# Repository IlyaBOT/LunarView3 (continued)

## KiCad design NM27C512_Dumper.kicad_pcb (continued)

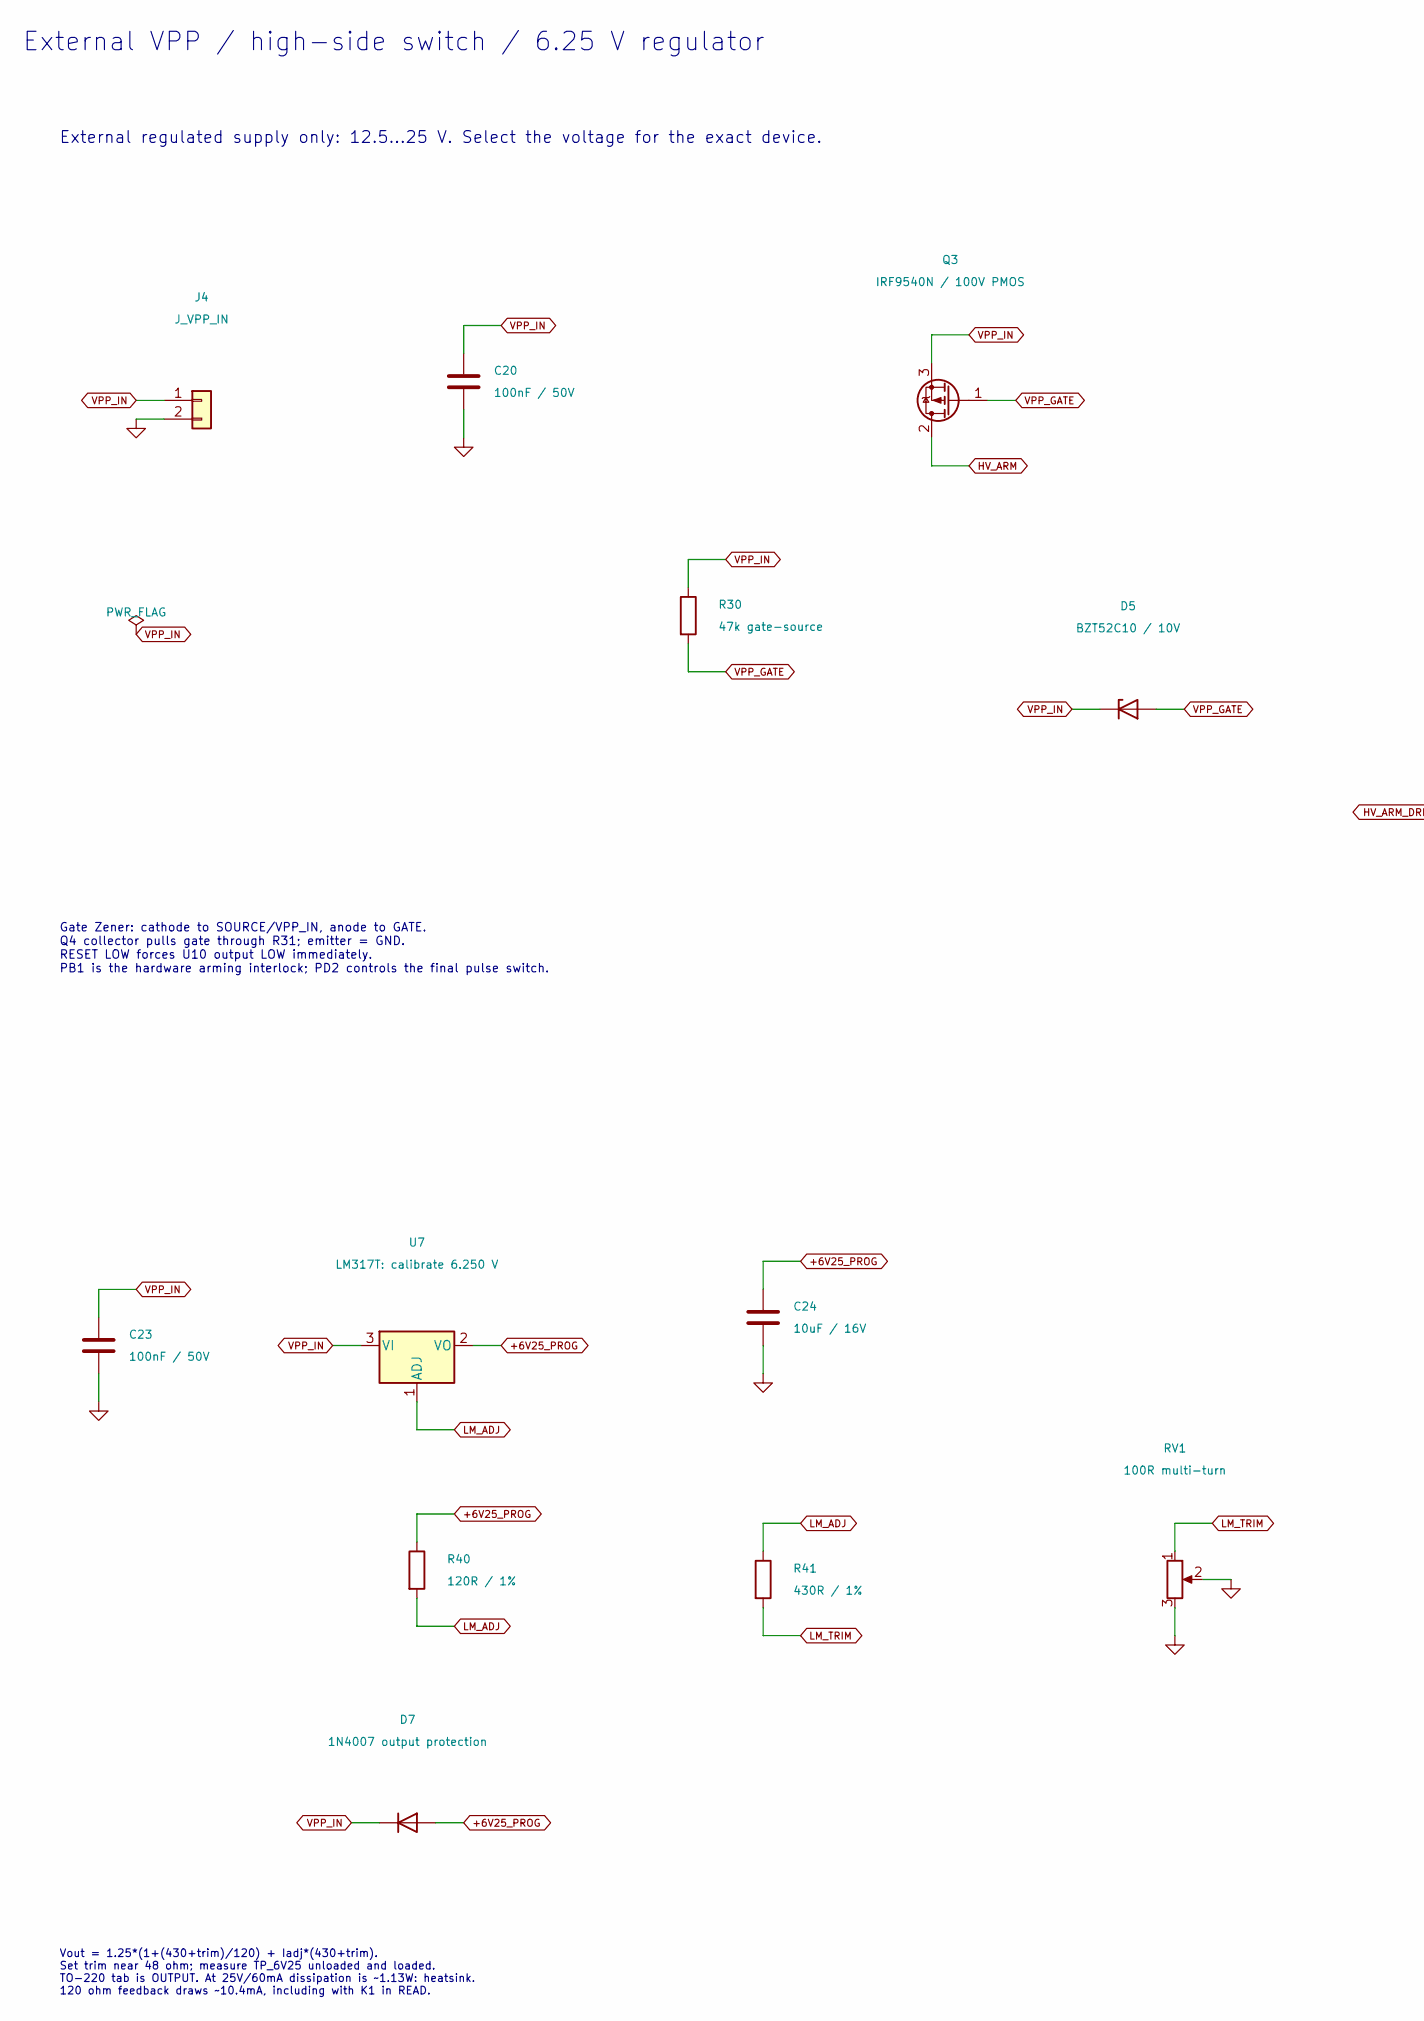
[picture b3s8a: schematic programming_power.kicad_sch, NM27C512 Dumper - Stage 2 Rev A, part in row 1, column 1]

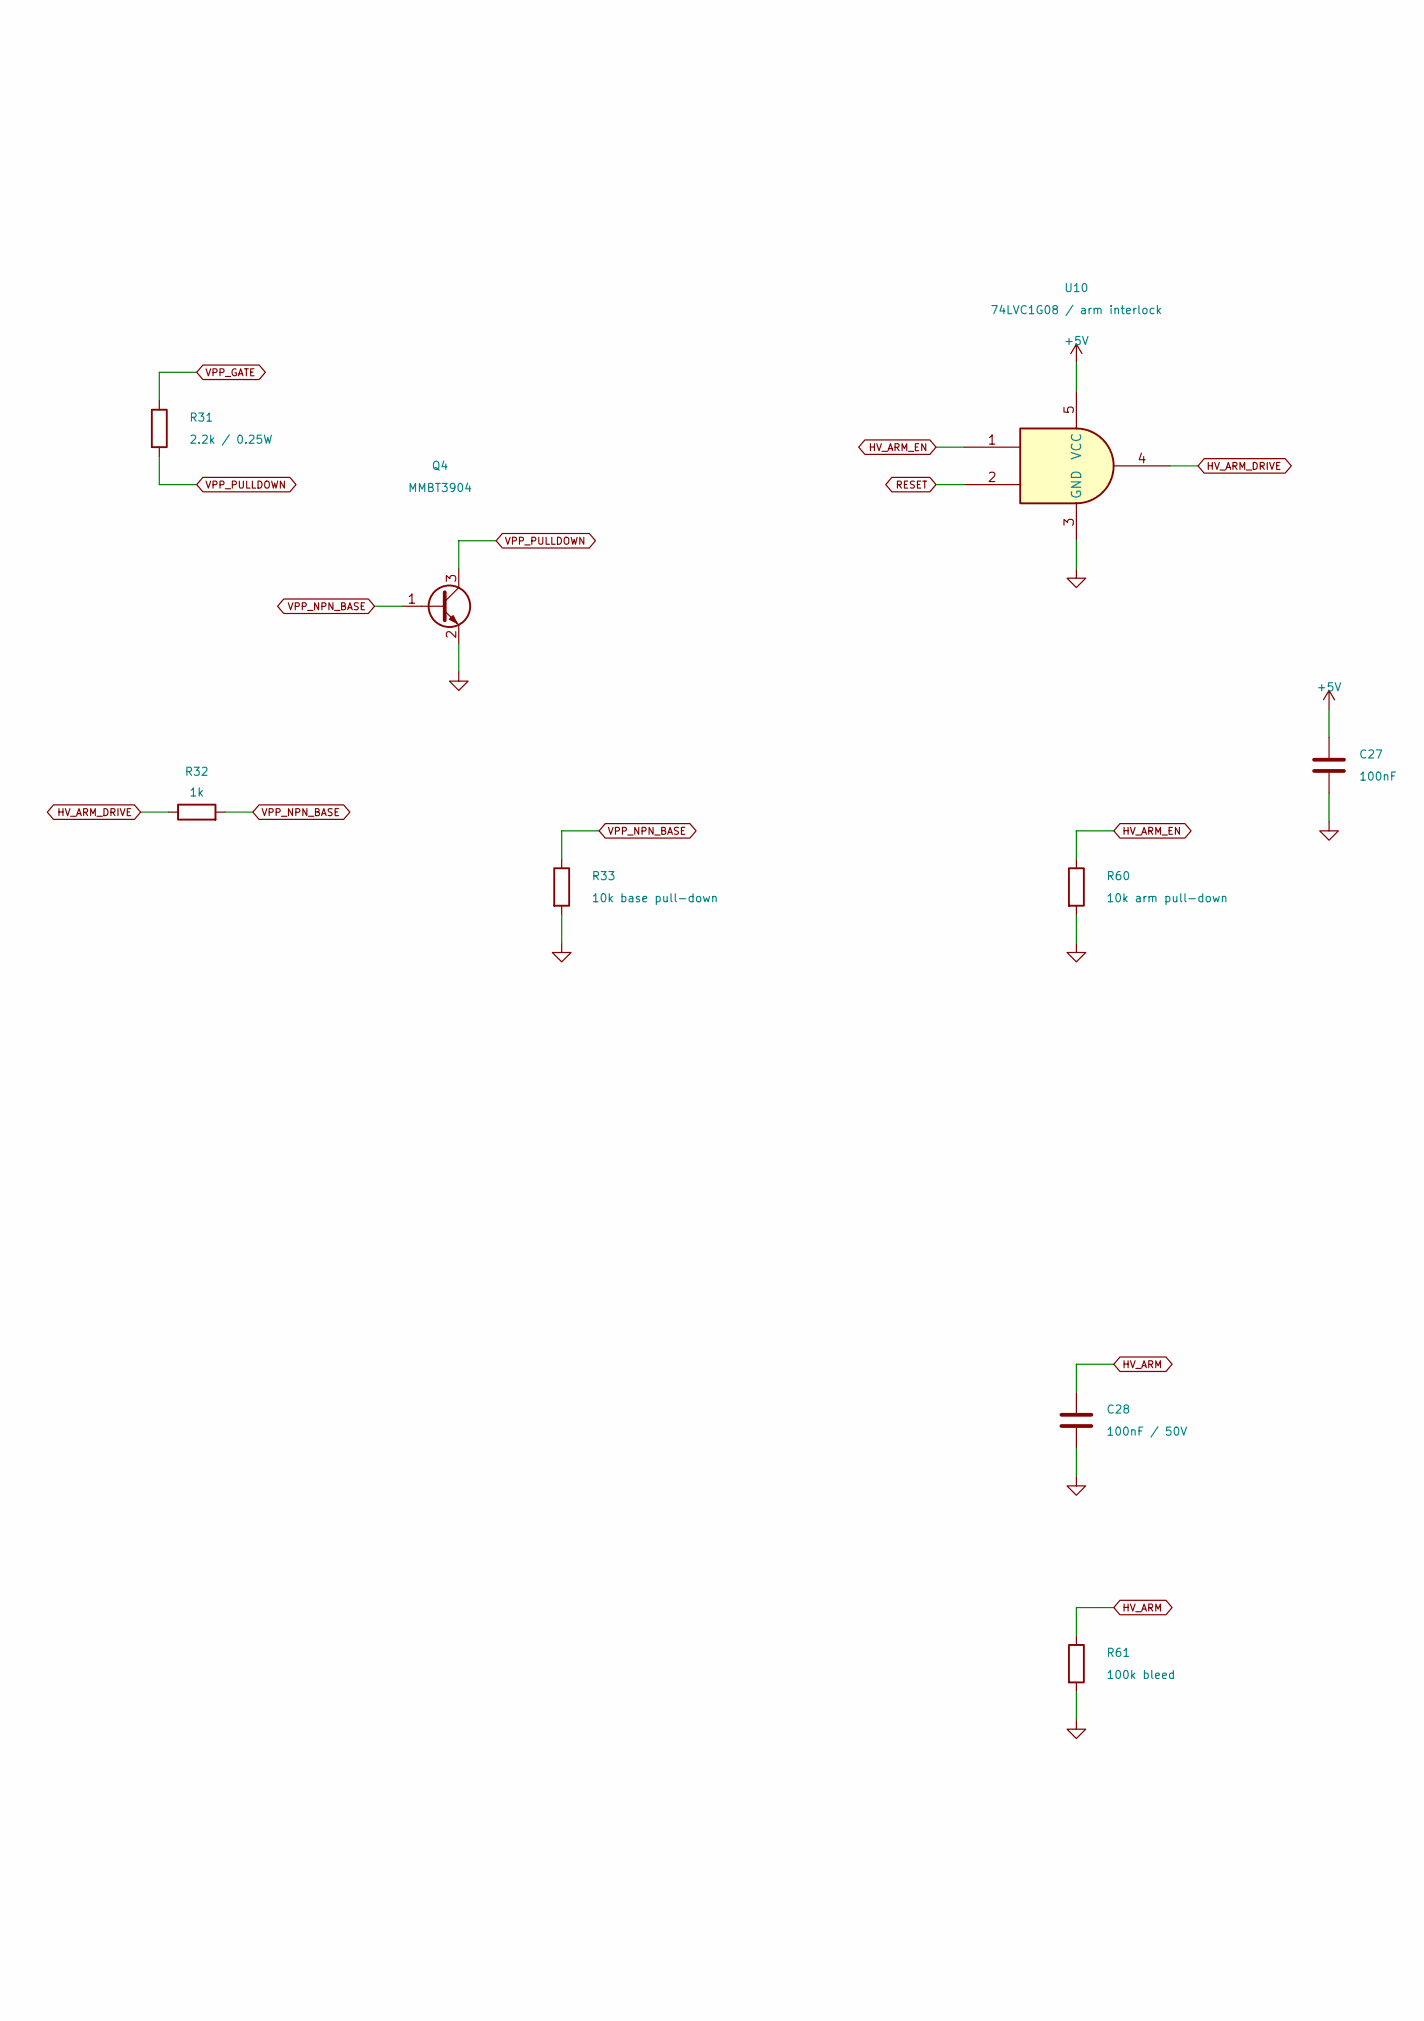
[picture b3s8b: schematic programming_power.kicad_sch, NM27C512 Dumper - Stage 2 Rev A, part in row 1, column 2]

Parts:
C20, C23, C28: 100nF / 50V; C_0603_1608Metric
C24: 10uF / 16V; C_1206_3216Metric
C27: 100nF; C_0603_1608Metric
D5: BZT52C10 / 10V; D_SOD-123
D7: 1N4007 output protection; D_DO-41_SOD81_P10.16mm_Horizontal
J4: J_VPP_IN; TerminalBlock_Phoenix_MKDS-1,5-2_1x02_P5.00mm_Horizontal
Q3: IRF9540N / 100V PMOS; TO-220-3_Vertical
Q4: MMBT3904; SOT-23
R30: 47k gate-source; R_0603_1608Metric
R31: 2.2k / 0.25W; R_1206_3216Metric
R32: 1k; R_0603_1608Metric
R33: 10k base pull-down; R_0603_1608Metric
R40: 120R / 1%; R_0603_1608Metric
R41: 430R / 1%; R_0603_1608Metric
R60: 10k arm pull-down; R_0603_1608Metric
R61: 100k bleed; R_0603_1608Metric
RV1: 100R multi-turn; Potentiometer_Bourns_3296W_Vertical
U7: LM317T: calibrate 6.250 V; TO-220-3_Vertical
U10: 74LVC1G08 / arm interlock; SOT-23-5

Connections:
+5V: C27.1, U10.5 (VCC); also elsewhere on the board
+6V25_PROG: C24.1, D7.2 (A), R40.1, U7.2 (VO); also elsewhere on the board
GND: C20.2, C23.2, C24.2, C27.2, C28.2, J4.2, Q4.2 (E), R33.2, R60.2, R61.2, RV1.2, RV1.3, U10.3 (GND); also elsewhere on the board
HV_ARM: C28.1, Q3.2 (D), R61.1; also elsewhere on the board
HV_ARM_DRIVE: R32.1, U10.4
HV_ARM_EN: R60.1, U10.1; also elsewhere on the board
LM_ADJ: R40.2, R41.1, U7.1 (ADJ)
LM_TRIM: R41.2, RV1.1
RESET: U10.2; also elsewhere on the board
VPP_GATE: D5.2 (A), Q3.1 (G), R30.2, R31.1
VPP_IN: C20.1, C23.1, D5.1 (K), D7.1 (K), J4.1, Q3.3 (S), R30.1, U7.3 (VI); also elsewhere on the board
VPP_NPN_BASE: Q4.1 (B), R32.2, R33.1
VPP_PULLDOWN: Q4.3 (C), R31.2

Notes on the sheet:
Vout = 1.25*(1+(430+trim)/120) + Iadj*(430+trim). Set trim near 48 ohm; measure TP_6V25 unloaded and loaded. TO-220 tab is OUTPUT. At 25V/60mA dissipation is ~1.13W: heatsink. 120 ohm feedback draws ~10.4mA, including with K1 in READ.
External regulated supply only: 12.5...25 V. Select the voltage for the exact device.
External VPP / high-side switch / 6.25 V regulator
Gate Zener: cathode to SOURCE/VPP_IN, anode to GATE. Q4 collector pulls gate through R31; emitter = GND. RESET LOW forces U10 output LOW immediately. PB1 is the hardware arming interlock; PD2 controls the final pulse switch.

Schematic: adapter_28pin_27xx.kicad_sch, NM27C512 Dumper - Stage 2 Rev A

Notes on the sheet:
Pin 01: 64/128/256: VPP; 512: A15
Pin 13: D2
Pin 08: A2
Pin 17: D5
Pin 05: A5
Pin 21: A10
Pin 14: GND
Pin 18: D6
2764/27128: pin27 is PGM#, NOT A14. 27256: pin27 is A14. Do not route a 595 output onto a VPP pin. Use keyed jumpers or a device-specific adapter. VPP on pin1 needs READ +5V selection, separate from the onboard NM27C512 relay. Read-only adapters may tie VPP and unused PGM# HIGH. WRITE remains disab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
Pin 03: A7
28-pin EPROM adapter reference
Pin 15: D3
Pin 27: 64/128: PGM#; 256/512: A14
Pin 16: D4
Pin 07: A3
Pin 04: A6
Pin 24: A9
Pin 02: A12
Pin 20: 64/128: CE#; 256/512: CE/PGM#
Pin 22: 64/128/256: OE#; 512: OE/VPP
REFERENCE ONLY - logical mapping for future adapter PCBs, not additional live targets
Pin 09: A1
Pin 06: A4
Pin 11: D0
Pin 12: D1
Pin 25: A8
Pin 23: A11
Pin 19: D7
Pin 10: A0
Pin 26: 64: NC; 128/256/512: A13
Pin 28: TARGET_VCC

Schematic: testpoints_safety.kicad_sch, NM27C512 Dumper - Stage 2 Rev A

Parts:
TP1: TP_5V; TestPoint_Pad_D1.5mm
TP2: TP_GND; TestPoint_Pad_D1.5mm
TP3: TP_6V25; TestPoint_Pad_D1.5mm
TP4: TP_VPP_IN; TestPoint_Pad_D1.5mm
TP5: TP_VPP_SW; TestPoint_Pad_D1.5mm
TP6: TP_RESET; TestPoint_Pad_D1.5mm
TP7: TP_ADDR_SCK; TestPoint_Pad_D1.5mm
TP8: TP_ADDR_LATCH; TestPoint_Pad_D1.5mm
TP9: TP_CE; TestPoint_Pad_D1.5mm
TP10: TP_OE; TestPoint_Pad_D1.5mm
TP11: TP_PGM; TestPoint_Pad_D1.5mm
TP12: TP_RX; TestPoint_Pad_D1.5mm
TP13: TP_TX; TestPoint_Pad_D1.5mm

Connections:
+5V: TP1.1 (1_1); also elsewhere on the board
+6V25_PROG: TP3.1 (1_1); also elsewhere on the board
ADDR_LATCH: TP8.1 (1_1); also elsewhere on the board
ADDR_SCK: TP7.1 (1_1); also elsewhere on the board
GND: TP2.1 (1_1); also elsewhere on the board
RESET: TP6.1 (1_1); also elsewhere on the board
TARGET_CE_PGM#: TP9.1 (1_1); also elsewhere on the board
TARGET_OE#: TP10.1 (1_1); also elsewhere on the board
TARGET_PGM#: TP11.1 (1_1); also elsewhere on the board
UART_RX: TP12.1 (1_1); also elsewhere on the board
UART_TX: TP13.1 (1_1); also elsewhere on the board
VPP_IN: TP4.1 (1_1); also elsewhere on the board
VPP_SW: TP5.1 (1_1); also elsewhere on the board

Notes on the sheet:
Test points and safety sequence
Safety sequence / required bench checks
1. USB supplies all 5V logic. External supply is regulated, current-limited and shares GND. 2. Power-up / RESET / ISP / DTR reset: CE and OE HIGH, relay READ, VPP disabled. 3. Preflight VPP measurement is made with relay in READ; onboard socket is isolated from VPP. 4. Verify target VCC before enab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

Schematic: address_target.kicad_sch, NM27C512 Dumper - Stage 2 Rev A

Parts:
C7, C8, C14: 100nF; C_0603_1608Metric
C9: 100nF / 16V; C_0603_1608Metric
C15: 10uF / 16V; C_0805_2012Metric
R2: 10k CE pull-up; R_0603_1608Metric
R3: 10k OE pull-up; R_0603_1608Metric
R7: 10k LATCH pull-down; R_0603_1608Metric
R8: 10k PGM pull-up; R_0603_1608Metric
U2, U3, U4: 74HC595D; SOIC-16_3.9x9.9mm_P1.27mm
U6: NM27C512Q SOCKET; DIP-28_W15.24mm_Socket_LongPads

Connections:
+5V: C7.1, C8.1, C14.1, R2.1, R3.1, R8.1, U2.10 (~SRCLR), U2.16 (VCC), U3.10 (~SRCLR), U3.16 (VCC), U4.10 (~SRCLR), U4.16 (VCC); also elsewhere on the board
A0: U2.15 (QA), U6.10 (A0); also elsewhere on the board
A1: U2.1 (QB), U6.9 (A1); also elsewhere on the board
A2: U2.2 (QC), U6.8 (A2); also elsewhere on the board
A3: U2.3 (QD), U6.7 (A3); also elsewhere on the board
A4: U2.4 (QE), U6.6 (A4); also elsewhere on the board
A5: U2.5 (QF), U6.5 (A5); also elsewhere on the board
A6: U2.6 (QG), U6.4 (A6); also elsewhere on the board
A7: U2.7 (QH), U6.3 (A7); also elsewhere on the board
A8: U3.15 (QA), U6.25 (A8); also elsewhere on the board
A9: U3.1 (QB), U6.24 (A9); also elsewhere on the board
A10: U3.2 (QC), U6.21 (A10); also elsewhere on the board
A11: U3.3 (QD), U6.23 (A11); also elsewhere on the board
A12: U3.4 (QE), U6.2 (A12); also elsewhere on the board
A13: U3.5 (QF), U6.26 (A13); also elsewhere on the board
A14: U3.6 (QG), U6.27 (A14); also elsewhere on the board
A15: U3.7 (QH), U6.1 (A15); also elsewhere on the board
A16: U4.15 (QA); also elsewhere on the board
A17: U4.1 (QB); also elsewhere on the board
A18: U4.2 (QC); also elsewhere on the board
A19: U4.3 (QD); also elsewhere on the board
ADDR_LATCH: R7.1, U2.12 (RCLK), U3.12 (RCLK), U4.12 (RCLK); also elsewhere on the board
ADDR_SCK: U2.11 (SRCLK), U3.11 (SRCLK), U4.11 (SRCLK); also elsewhere on the board
ADDR_SER: U2.14 (SER); also elsewhere on the board
CASCADE_1: U2.9 (QH'), U3.14 (SER)
CASCADE_2: U3.9 (QH'), U4.14 (SER)
GND: C7.2, C8.2, C9.2, C14.2, C15.2, R7.2, U2.8 (GND), U2.13 (~OE), U3.8 (GND), U3.13 (~OE), U4.8 (GND), U4.13 (~OE), U6.14 (GND); also elsewhere on the board
SOCKET_OE_VPP: U6.22 (~OE); also elsewhere on the board
STATUS_BLUE: U4.6 (QG); also elsewhere on the board
STATUS_GREEN: U4.5 (QF); also elsewhere on the board
STATUS_RED: U4.4 (QE); also elsewhere on the board
TARGET_CE_PGM#: R2.2, U6.20 (~CE); also elsewhere on the board
TARGET_D0: U6.11 (D0); also elsewhere on the board
TARGET_D1: U6.12 (D1); also elsewhere on the board
TARGET_D2: U6.13 (D2); also elsewhere on the board
TARGET_D3: U6.15 (D3); also elsewhere on the board
TARGET_D4: U6.16 (D4); also elsewhere on the board
TARGET_D5: U6.17 (D5); also elsewhere on the board
TARGET_D6: U6.18 (D6); also elsewhere on the board
TARGET_D7: U6.19 (D7); also elsewhere on the board
TARGET_OE#: R3.2; also elsewhere on the board
TARGET_PGM#: R8.2; also elsewhere on the board
TARGET_VCC: C9.1, C15.1, U6.28 (VCC); also elsewhere on the board

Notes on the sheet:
Address / status shift registers: SPI shifts while latch stays LOW
Send U4 byte first, U3 byte second, U2 byte last; MSB first. U2 Q0-Q7 = A0-A7; U3 Q0-Q7 = A8-A15. Stage 2: U4 Q0-Q3 = A16-A19; Q4/Q5/Q6 = active-low R/G/B. OE# = GND and SRCLR# = +5V on every 595.
Direct socket U6 is dedicated to NM27C512. One target only: socket OR adapter. Pin 20 = CE/PGM#; pin 22 = OE/VPP via K1. READ: +5V, OE logic. PROG: +6.25V, switched VPP. Do not insert/remove a target with USB or VPP connected.
Address generator and NM27C512 direct socket

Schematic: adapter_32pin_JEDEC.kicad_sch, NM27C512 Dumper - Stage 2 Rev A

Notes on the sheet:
Pin 23: A10
Pin 14: D1
Pin 22: CE / CE-PGM# (family dependent)
Pin 18: D4
Pin 08: A4
Pin 09: A3
Pin 10: A2
Pin 27: A8
Pin 07: A5
32-pin JEDEC adapter reference
Pin 19: D5
Pin 11: A1
Pin 17: D3
Pin 05: A7
Pin 25: A11
National 27C010/020/040/080 package comparison is the source for these pin roles. Use a device-specific adapter; role changes require keyed selection or HV-rated switching. Pin1 must never receive VPP when it is A19. Pin24 changes from OE to OE/VPP on 080. 27C080 cannot use a generic 32-pin VPP-pin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
Pin 02: A16
Pin 01: 010/020/040: VPP; 080: A19
Pin 06: A6
Pin 15: D2
Pin 29: A14
Pin 32: TARGET_VCC
Pin 28: A13
Pin 20: D6
Pin 31: 010/020: PGM#; 040/080: A18
Pin 03: A15
Pin 04: A12
Pin 13: D0
REFERENCE ONLY - logical mapping for future adapter PCBs, not additional live targets
Pin 12: A0
Pin 21: D7
Pin 26: A9
Pin 30: 010: NC; 020/040/080: A17
Pin 24: 010/020/040: OE#; 080: OE/VPP
Pin 16: GND

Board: 2 copper layers, 143 parts (0 on the bottom side), 113 nets, no tracks yet.

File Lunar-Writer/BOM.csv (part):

Reference,Value,Footprint,Datasheet
C1,10uF / 10V,Capacitor_SMD:C_0805_2012Metric,
C10,100nF,Capacitor_SMD:C_0603_1608Metric,
C11,22pF,Capacitor_SMD:C_0603_1608Metric,
C12,22pF,Capacitor_SMD:C_0603_1608Metric,
C13,100nF auto-reset,Capacitor_SMD:C_0603_1608Metric,
C14,100nF,Capacitor_SMD:C_0603_1608Metric,
C15,10uF / 16V,Capacitor_SMD:C_0805_2012Metric,
C2,100nF,Capacitor_SMD:C_0603_1608Metric,
C20,100nF / 50V,Capacitor_SMD:C_0603_1608Metric,
C21,100nF,Capacitor_SMD:C_0603_1608Metric,
C22,10nF,Capacitor_SMD:C_0603_1608Metric,
C23,100nF / 50V,Capacitor_SMD:C_0603_1608Metric,
C24,10uF / 16V,Capacitor_SMD:C_1206_3216Metric,
C25,10nF,Capacitor_SMD:C_0603_1608Metric,
C26,100nF,Capacitor_SMD:C_0603_1608Metric,
C27,100nF,Capacitor_SMD:C_0603_1608Metric,
C28,100nF / 50V,Capacitor_SMD:C_0603_1608Metric,
C3,100nF,Capacitor_SMD:C_0603_1608Metric,
C30,220uF / 50V low ESR,ProjectFootprints:Writer_C30_CP_Radial_D10.0mm_P5.00mm,
C31,100nF / 50V X7R,Capacitor_SMD:C_0805_2012Metric,
C32,680uF / 50V low ESR,ProjectFootprints:Writer_C32_CP_Radial_D12.5mm_P5.00mm,
C33,100nF / 50V X7R,Capacitor_SMD:C_0805_2012Metric,
C34,47uF / 16V compensation,ProjectFootprints:Writer_C34_CP_Radial_D5.0mm_P2.00mm,
C35,1uF / 50V X7R,Capacitor_SMD:C_1206_3216Metric,
C36,1uF / 50V X7R,Capacitor_SMD:C_1206_3216Metric,
C4,100nF,Capacitor_SMD:C_0603_1608Metric,
C5,100nF,Capacitor_SMD:C_0603_1608Metric,
C6,100nF,Capacitor_SMD:C_0603_1608Metric,
C7,100nF,Capacitor_SMD:C_0603_1608Metric,
C8,100nF,Capacitor_SMD:C_0603_1608Metric,
C9,100nF / 16V,Capacitor_SMD:C_0603_1608Metric,
D10,BAT54S,Package_TO_SOT_SMD:SOT-23,https://www.diodes.com/assets/Datasheets/ds11005.pdf
D11,BAT54S,Package_TO_SOT_SMD:SOT-23,https://www.diodes.com/assets/Datasheets/ds11005.pdf
D12,BAT54S,Package_TO_SOT_SMD:SOT-23,https://www.diodes.com/assets/Datasheets/ds11005.pdf
D13,BAT54S,Package_TO_SOT_SMD:SOT-23,https://www.diodes.com/assets/Datasheets/ds11005.pdf
D14,BAT54S,Package_TO_SOT_SMD:SOT-23,https://www.diodes.com/assets/Datasheets/ds11005.pdf
D15,BAT54S,Package_TO_SOT_SMD:SOT-23,https://www.diodes.com/assets/Datasheets/ds11005.pdf
D16,BAT54S,Package_TO_SOT_SMD:SOT-23,https://www.diodes.com/assets/Datasheets/ds11005.pdf
D17,BAT54S,Package_TO_SOT_SMD:SOT-23,https://www.diodes.com/assets/Datasheets/ds11005.pdf
D2,RGB CA / 5050 OR THT5,ProjectFootprints:Writer_D2_RGB_CA_5050_or_THT5,https://www.kingbright.com/attachments/file/psearch/000/00/2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
D20,BAT54S,Package_TO_SOT_SMD:SOT-23,https://www.diodes.com/assets/Datasheets/ds11005.pdf
D21,BAT54S,Package_TO_SOT_SMD:SOT-23,https://www.diodes.com/assets/Datasheets/ds11005.pdf
D22,BAT54S,Package_TO_SOT_SMD:SOT-23,https://www.diodes.com/assets/Datasheets/ds11005.pdf
D23,BAT54S,Package_TO_SOT_SMD:SOT-23,https://www.diodes.com/assets/Datasheets/ds11005.pdf
D24,BAT54S,Package_TO_SOT_SMD:SOT-23,https://www.diodes.com/assets/Datasheets/ds11005.pdf
D25,BAT54S,Package_TO_SOT_SMD:SOT-23,https://www.diodes.com/assets/Datasheets/ds11005.pdf
D26,BAT54S,Package_TO_SOT_SMD:SOT-23,https://www.diodes.com/assets/Datasheets/ds11005.pdf
D27,BAT54S,Package_TO_SOT_SMD:SOT-23,https://www.diodes.com/assets/Datasheets/ds11005.pdf
D3,RX BLUE,LED_SMD:LED_0603_1608Metric,
D30,ADC6 BAT54S clamp,Package_TO_SOT_SMD:SOT-23,https://www.diodes.com/assets/Datasheets/ds11005.pdf
D31,ADC7 BAT54S clamp,Package_TO_SOT_SMD:SOT-23,https://www.diodes.com/assets/Datasheets/ds11005.pdf
D4,TX ORANGE,LED_SMD:LED_0603_1608Metric,
D40,SS36 / 3A / 60V reverse-polarity,Diode_SMD:D_SMA,
D41,SMBJ24A / TVS,Diode_SMD:D_SMB,
D42,SS36 / 3A / 60V boost rectifier,Diode_SMD:D_SMA,
D43,M7 / 1N4007-SMD / 1A 1000V,Diode_SMD:D_SMA,
D44,M7 / 1N4007-SMD / 1A 1000V,Diode_SMD:D_SMA,
D5,BZT52C10 / 10V,Diode_SMD:D_SOD-123,
D6,VPP ACTIVE RED,LED_SMD:LED_0603_1608Metric,
D7,1N4007 output protection,ProjectFootprints:Writer_D7_D_DO-41_SOD81_P10.16mm_Horizontal,
D8,1N4148WS flyback,Diode_SMD:D_SOD-323,
D9,BAT54WS RESET clamp,Diode_SMD:D_SOD-323,
F1,500mA hold,Fuse:Fuse_1812_4532Metric,
F2,MF-R090 / 0.9A hold / 60V,ProjectFootprints:PTC_MF_R090,
J1,USB Micro-B,ProjectFootprints:Writer_J1_USB_Micro-B_Molex-105017-0001,
J2,AVR ISP,ProjectFootprints:Writer_J2_PinHeader_2x03_P2.54mm_Vertical,
J3,UART (MCU RX/TX),ProjectFootprints:Writer_J3_PinHeader_1x03_P2.54mm_Vertical,
J4,12-24V DC IN (+ / GND),"ProjectFootprints:Writer_J4_TerminalBlock_Phoenix_MKDS-1,5-2_1x02_P5.00mm_Horizontal",
J5,J_TARGET / 40-pin,ProjectFootprints:Writer_J5_PinHeader_2x20_P2.54mm_Vertical,
JP1,VPP SELECT: 12.75 / common / HIGH,ProjectFootprints:Writer_JP1_PinHeader_1x03_P2.54mm_Vertical,
K1,G5V-2-DC5 (100mA coil),ProjectFootprints:Writer_K1_Relay_DPDT_Omron_G5V-2,http://omronfs.omron.com/en_US/ecb/products/pdf/en-g5v_2.pdf
L1,100uH / SRR1210A-101M / Isat 2.2A,ProjectFootprints:Writer_L1_L_Bourns_SRR1210A,
Q1,MMBT3906,Package_TO_SOT_SMD:SOT-23,https://www.onsemi.com/pdf/datasheet/pzt3906-d.pdf
Q2,MMBT3906,Package_TO_SOT_SMD:SOT-23,https://www.onsemi.com/pdf/datasheet/pzt3906-d.pdf
Q3,IRF9540N / 100V PMOS,ProjectFootprints:Writer_Q3_TO-220-3_Vertical,http://www.irf.com/product-info/datasheets/data/irf9540n.pdf
Q4,MMBT5551 / 160V NPN,Package_TO_SOT_SMD:SOT-23,https://www.onsemi.com/pdf/datasheet/pzt3904-d.pdf
Q5,MMBT3904,Package_TO_SOT_SMD:SOT-23,https://www.onsemi.com/pdf/datasheet/pzt3904-d.pdf
Q6,MMBT5551 / 160V NPN,Package_TO_SOT_SMD:SOT-23,
Q7,MMBT5401 / 150V PNP,Package_TO_SOT_SMD:SOT-23,
R1,10k,Resistor_SMD:R_0603_1608Metric,
R10,1k,Resistor_SMD:R_0603_1608Metric,
R11,1k,Resistor_SMD:R_0603_1608Metric,
R12,1k,Resistor_SMD:R_0603_1608Metric,
R13,1k,Resistor_SMD:R_0603_1608Metric,
R14,1k,Resistor_SMD:R_0603_1608Metric,
R15,1k,Resistor_SMD:R_0603_1608Metric,
R16,1k,Resistor_SMD:R_0603_1608Metric,
R17,1k,Resistor_SMD:R_0603_1608Metric,
R2,10k CE pull-up,Resistor_SMD:R_0603_1608Metric,
R20,1k,Resistor_SMD:R_0603_1608Metric,
R21,1k,Resistor_SMD:R_0603_1608Metric,
R22,1k,Resistor_SMD:R_0603_1608Metric,
R23,10k,Resistor_SMD:R_0603_1608Metric,
R24,10k,Resistor_SMD:R_0603_1608Metric,
R25,1k,Resistor_SMD:R_0603_1608Metric,
R26,1k,Resistor_SMD:R_0603_1608Metric,
R3,10k OE pull-up,Resistor_SMD:R_0603_1608Metric,
R30,47k gate-source,Resistor_SMD:R_0603_1608Metric,
R31,2.2k / 0.5W,Resistor_SMD:R_2010_5025Metric,
R32,1k,Resistor_SMD:R_0603_1608Metric,
R33,10k base pull-down,Resistor_SMD:R_0603_1608Metric,
R34,10k VPP_EN pull-down,Resistor_SMD:R_0603_1608Metric,
R35,120k / 1%,Resistor_SMD:R_0603_1608Metric,
R36,22k / 1%,Resistor_SMD:R_0603_1608Metric,
R37,10k bleed / 0.25W,Resistor_SMD:R_1206_3216Metric,
R38,5.1k,Resistor_SMD:R_0603_1608Metric,
R39,5.1k,Resistor_SMD:R_0603_1608Metric,
R4,1k,Resistor_SMD:R_0603_1608Metric,
R40,120R / 1%,Resistor_SMD:R_0603_1608Metric,
R41,430R / 1%,Resistor_SMD:R_0603_1608Metric,
R42,470R relay drive,Resistor_SMD:R_0603_1608Metric,
R43,10k,Resistor_SMD:R_0603_1608Metric,
R44,10k,Resistor_SMD:R_0603_1608Metric,
R45,10k / 1%,Resistor_SMD:R_0603_1608Metric,
R46,10k / 1%,Resistor_SMD:R_0603_1608Metric,
R5,1k,Resistor_SMD:R_0603_1608Metric,
R50,1k,Resistor_SMD:R_0603_1608Metric,
R51,1k,Resistor_SMD:R_0603_1608Metric,
R52,1k,Resistor_SMD:R_0603_1608Metric,
R53,1k,Resistor_SMD:R_0603_1608Metric,
R54,1k,Resistor_SMD:R_0603_1608Metric,
R55,1k,Resistor_SMD:R_0603_1608Metric,
R56,1k,Resistor_SMD:R_0603_1608Metric,
R57,1k,Resistor_SMD:R_0603_1608Metric,
R60,10k arm pull-down,Resistor_SMD:R_0603_1608Metric,
R61,100k bleed,Resistor_SMD:R_0603_1608Metric,
R62,10k base-emitter,Resistor_SMD:R_0603_1608Metric,
R63,2.2k / 0.5W,Resistor_SMD:R_2010_5025Metric,
R64,1k,Resistor_SMD:R_0603_1608Metric,
R65,10k,Resistor_SMD:R_0603_1608Metric,
R7,10k LATCH pull-down,Resistor_SMD:R_0603_1608Metric,
R70,47k / 1%,Resistor_SMD:R_0603_1608Metric,
R71,2k / 1%,Resistor_SMD:R_0603_1608Metric,
R72,470R compensation,Resistor_SMD:R_0603_1608Metric,
R73,120R / 1%,Resistor_SMD:R_0603_1608Metric,
R74,1k / 1%,Resistor_SMD:R_0603_1608Metric,
R75,120R / 1%,Resistor_SMD:R_0603_1608Metric,
R76,1.8k / 1%,Resistor_SMD:R_0603_1608Metric,
R77,100k bleed,Resistor_SMD:R_0603_1608Metric,
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
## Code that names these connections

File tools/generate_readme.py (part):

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    mcu=next(p for p in bom if p['ref']=='U1')['nets']
    eprom=next(p for p in bom if p['ref']=='U6')['nets']
    header=json.loads((ROOT/'validation/target_header.json').read_text())
    gpio=['PD3','PD4','GND','VCC','GND','VCC','PB6 / XTAL1','PB7 / XTAL2','PD5','PD6','PD7','PB0','PB1','PB2','PB3 / MOSI','PB4 / MISO',
          'PB5 / SCK','AVCC','ADC6','AREF','GND','ADC7','PC0','PC1','PC2','PC3','PC4','PC5','PC6 / RESET','PD0 / RXD','PD1 / TXD','PD2']
    group=defaultdict(list)
    for part in bom:group[part['value'],part['footprint']].append(part['ref'])
    bom_table=table(['Refs','Qty','Value / exact part','KiCad footprint'],[(', '.join(refs),len(refs),value,fp) for (value,fp),refs in group.items()])
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
## ATmega328P-AU TQFP32 map

PB1, originally reserved for an interlock, now explicitly controls HV_ARM_EN. PB4/MISO is used only by ISP. ADC6/ADC7 are analog-only package pins.

'''+table(['Package pin','Function','Net'],[(i,gpio[i-1],mcu[str(i)]) for i in range(1,33)])+'''
## Address and status chain
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| Q1 / pin1 | A1 | A9 | A17 |
| Q2 / pin2 | A2 | A10 | A18 |
| Q3 / pin3 | A3 | A11 | A19 |
| Q4 / pin4 | A4 | A12 | STATUS_RED |
| Q5 / pin5 | A5 | A13 | STATUS_GREEN |
| Q6 / pin6 | A6 | A14 | STATUS_BLUE |
| Q7 / pin7 | A7 | A15 | NC / reserved |

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
'''+table(['Pin','Net','Pin','Net'],[(i,eprom[str(i)],29-i,eprom[str(29-i)]) for i in range(1,15)])+'''
In READ, TARGET_VCC=+5V and SOCKET_OE_VPP follows TARGET_OE#. In PROGRAM, TARGET_VCC=+6.25V and SOCKET_OE_VPP=VPP_SW. Pin20 CE/PGM# is the programming-pulse input. R2/R3/R8 pull CE/OE/PGM HIGH from the logic rail during RESET. K1 physically disconnects the MCU OE path from VPP.

## Headers and UART

J2 is the standard AVR ISP 2x3: pin1 MISO, 2 +5V, 3 SCK, 4 MOSI, 5 RESET, 6 GND. J3 is a 1x3 header: **1 GND, 2 RX (MCU PD0), 3 TX (MCU PD1)**. An external UART TX goes to J3 RX and external RX to J3 TX. Use 5 V TTL and avoid simultaneous active TX sources.

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
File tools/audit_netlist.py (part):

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            expect('U9',{i+2:'HCT_A'+str(i),18-i:'HCT_B'+str(i)})
            expect('R'+str(50+i),{1:'TARGET_D'+str(i),2:'HCT_B'+str(i)})
            expect('D'+str(20+i),{1:'GND',2:'+5V',3:'HCT_B'+str(i)})
        for ref,mapping in {'R35':{1:'VPP_SW',2:'VPP_SENSE'},'R36':{1:'VPP_SENSE',2:'GND'},
                            'R45':{1:'TARGET_VCC',2:'TARGET_VCC_SENSE'},'R46':{1:'TARGET_VCC_SENSE',2:'GND'}}.items():expect(ref,mapping)
        header={i+1:'A'+str(i) for i in range(20)}
        header.update({21+i:'TARGET_D'+str(i) for i in range(8)})
        header.update(dict(zip(range(29,41),['TARGET_CE_PGM#','TARGET_OE#','TARGET_PGM#','VPP_SW','TARGET_VCC','+5V','+6V25_PROG','GND','PROG_MODE','GND','RESET','GND'])))
        expect('J5',header)
        for name in ['VPP_IN','VPP_GATE','VPP_PULLDOWN','HV_ARM','VPP_SW','PULSE_PNP_BASE','PULSE_PULLDOWN','+6V25_PROG','TARGET_VCC','SOCKET_OE_VPP']:
            check(not any(ref=='U1' for ref,pin in nets.get(name,set())),f'No direct high voltage net {name} at U1')
        check(nets['ISP_MISO']=={('U1','16'),('J2','1')},'PB4/MISO used only for ISP')
    else:
        check(not any(name in nets for name in ['VPP_IN','VPP_SW','+6V25_PROG','HV_ARM']),'Baseline contains no programming rails')
    components={c.attrib['ref']:c for c in tree.findall('./components/comp')}
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
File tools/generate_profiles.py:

"""Single source of truth: generate JSON profiles and a compact AVR flash table."""
from pathlib import Path
import hashlib
import json

ROOT=Path(__file__).resolve().parents[1]
NATIONAL='https://deramp.com/downloads/mfe_archive/050-Component%20Specifications/National%20Semiconductor/Memory%20Components/'
INTEL='https://deramp.com/downloads/mfe_archive/050-Component%20Specifications/Intel/Memory%20Components/'

def profile(name, bits, package, adapter, source=None, aliases=(), verified=False):
    return dict(name=name,aliases=list(aliases),package=package,adapter=adapter,size_bytes=1<<bits,data_bits=8,address_bits=bits,
        read_supported=verified,read_vcc=5.0,read_vpp=5.0,program_supported=False,program_vcc=None,program_vpp=None,vpp_tolerance=None,
        address_pin_map={},data_pin_map={},ce_role=None,oe_role=None,pgm_role=None,vpp_pin_role=None,
        program_pulse_us=None,max_program_pulses=None,verify_algorithm=None,power_sequence=['USB logic first','controls inactive','VPP off','READ relay'],
        sources=[source] if source else [],pinout_verified=verified,read_profile_verified=verified,program_algorithm_verified=False,
        hardware_commissioned=False,read_access_delay_us=10,notes=[])

def map24(p, is2732=False):
    p['address_pin_map']={f'A{i}':8-i for i in range(8)}
    p['address_pin_map'].update(A8=23,A9=22,A10=19)
    if is2732:p['address_pin_map']['A11']=21
    p['data_pin_map']={f'D{i}':n for i,n in enumerate([9,10,11,13,14,15,16,17])}
    p.update(ce_role={'pin':18,'net':'TARGET_CE_PGM#','read_active':0},oe_role={'pin':20,'net':'TARGET_OE#','read_active':0},
        pgm_role={'pin':18,'note':'manufacturer-specific; write disabled'},vpp_pin_role={'pin':20 if is2732 else 21,'read':'OE logic' if is2732 else 'tie to TARGET_VCC (+5V)'},
        vcc_pin=24,gnd_pin=12)

def map28(p,bits):
    full={0:10,1:9,2:8,3:7,4:6,5:5,6:4,7:3,8:25,9:24,10:21,11:23,12:2,13:26,14:27,15:1}
    p['address_pin_map']={f'A{i}':full[i] for i in range(bits)}
    p['data_pin_map']={f'D{i}':n for i,n in enumerate([11,12,13,15,16,17,18,19])}
    p.update(ce_role={'pin':20,'net':'TARGET_CE_PGM#','read_active':0},oe_role={'pin':22,'net':'TARGET_OE#','read_active':0},
        pgm_role={'pin':20 if bits>=15 else 27,'net':'TARGET_CE_PGM#' if bits>=15 else 'TARGET_PGM#','inactive':1},
        vpp_pin_role={'pin':22 if bits==16 else 1,'read':'OE logic' if bits==16 else 'tie to TARGET_VCC (+5V)'},vcc_pin=28,gnd_pin=14)
    if bits==13:p['unused_pins']={'26':'NC'}

def map32(p,bits):
    full={0:12,1:11,2:10,3:9,4:8,5:7,6:6,7:5,8:27,9:26,10:23,11:25,12:4,13:28,14:29,15:3,16:2,17:30,18:31,19:1}
    p['address_pin_map']={f'A{i}':full[i] for i in range(bits)}
    p['data_pin_map']={f'D{i}':n for i,n in enumerate([13,14,15,17,18,19,20,21])}
    p.update(ce_role={'pin':22,'net':'TARGET_CE_PGM#','read_active':0},oe_role={'pin':24,'net':'TARGET_OE#','read_active':0},
        pgm_role={'pin':31 if bits<=18 else 22,'note':'National package comparison only; programming disabled'},
        vpp_pin_role={'pin':24 if bits==20 else 1,'read':'OE logic' if bits==20 else 'tie to TARGET_VCC (+5V)'},vcc_pin=32,gnd_pin=16)

def generate():
    profiles=[]
    p=profile('NM27C512',16,'DIP-28 600mil','onboard_U6',NATIONAL+'National%20NM27C512.pdf',['NM27C512Q','NM27C512N'],True)
    map28(p,16)
    p.update(program_supported=True,program_vcc=6.25,program_vpp=12.75,vpp_tolerance=0.25,
        program_vcc_min=6.0,program_vcc_max=6.5,program_vpp_min=12.5,program_vpp_max=13.0,program_vpp_absolute_max=14.0,
        program_temperature_c=[20,30],program_pulse_us=100,max_program_pulses=25,program_algorithm_verified=True,
        verify_algorithm='National Fast Algorithm: verify after every pulse at VCC=6.25V / OE-VPP=VIL; final whole-image compare at VCC=5V',
        power_sequence=['inactive controls and input data','arm internal HV with relay READ','test VPP_SW with socket isolated','VPP off and discharge verified',
            'relay PROGRAM; check 6.25V','for each byte: enable VPP; drive data; CE low 100us; CE high; input data; VPP off; discharge; verify byte',
            'VPP off; internal HV off; relay READ; compare all bytes at 5V'],
        notes=['Source: National TL/D/10834 February 1994, pages 2,5,6,7.',
            'Default firmware WRITE lock requires bench commissioning; algorithm verified does not mean hardware tested.',
            'Source OCR renders microseconds as ms; original page images explicitly show 100 us.',
            'Source final verification is 5.0V +/-5%; no universal overprogram pulse is specified.'])
    profiles.append(p)
    p=profile('27C512',16,'DIP-28 600mil','onboard_U6 (read compatibility only)',NATIONAL+'National%20NM27C512.pdf',[],True);map28(p,16)
    p['notes']=['Generic compatible read pinout only. WRITE requires an explicit manufacturer profile; use NM27C512 only for a marked National/Fairchild part.'];profiles.append(p)
    for name,bits in [('2716',11),('2732',12),('2764',13),('27128A',14),('27256',15)]:
        p=profile('INTEL'+name,bits,'DIP-'+('24' if bits<13 else '28'),'adapter_'+('2716_KR573RF5' if bits<13 else '28pin_27xx'),
            INTEL+'Intel%20'+name+'.pdf',[name]+(['27128'] if bits==14 else []),True)
        (map24(p,bits==12) if bits<13 else map28(p,bits))
        p['notes']=['Read mode and physical pinout verified against this Intel datasheet. Exact write algorithm is not implemented; WRITE disabled.']
        profiles.append(p)
    p=profile('KR573RF5',11,'DIP-24','adapter_2716_KR573RF5',None,['K573RF5','KR573RF5','КР573РФ5','К573РФ5'],False)
    p.update(expected_programming_vpp=25.0,verification_pending='Original manufacturer pinout/read specification and algorithm have not been located.')
    p['notes']=['Requested 2KiB x8 / A0-A10 profile is present but READ and WRITE are quarantined. No Intel pinout is silently substituted for KR573RF5.']
    profiles.append(p)
    for bits in range(17,21):
        suffix={17:'010',18:'020',19:'040',20:'080'}[bits]
        sources={17:'https://datasheets.pl/elementy_czynne/IC/NM/NM27C010-2.pdf',
                 18:'https://www.pselectronic.cz/pdf/1125/11250125.pdf',
                 19:'https://docs.rs-online.com/a680/0900766b80025540.pdf',
                 20:NATIONAL+'National%20NM27C512.pdf'}
        p=profile('NM27C'+suffix,bits,'DIP-32','adapter_32pin_JEDEC',sources[bits],['27C'+suffix],bits<20)
        map32(p,bits);p['pinout_verified']=True
        p['notes']=['Pinout and 5V read mode verified against the exact National/Fairchild datasheet. VPP pin1 tied to TARGET_VCC for READ; WRITE disabled.'] if bits<20 else [
            'Package roles verified in NM27C512 family comparison on page 2. Individual read operating limits/algorithm require an exact device datasheet; commands disabled.']
        if bits==17:p['unused_pins']={'30':'XX / do not connect on read adapter'}
        profiles.append(p)
    result={'schema_version':1,'hardware_revision':'A','profiles':profiles,
        'unsupported':{'2708':'Requires +12V and -5V in addition to +5V even for read; unsupported power architecture.',
                       '27C160':'16-bit data bus; Rev A is 8-bit only.'}}
    text=json.dumps(result,ensure_ascii=False,indent=2)+'\n'
    # Keep canonical LF bytes on Windows: firmware hash must match the actual host file.
    (ROOT/'device_profiles.json').write_bytes(text.encode('utf8'))
    digest=hashlib.sha256(text.encode()).hexdigest()[:16]
    header=['/* Generated from device_profiles.json by tools/generate_profiles.py. */', '#pragma once', '#include <stdint.h>','#include <avr/pgmspace.h>',
        '#define PROFILE_HASH "'+digest+'"', '#define PROFILE_COUNT '+str(len(profiles)),
        'typedef struct { char name[16]; uint32_t size; uint8_t address_bits, read_ok, program_ok, algorithm; uint16_t read_min_mv, read_max_mv, vcc_min_mv, vcc_max_mv, vpp_min_mv, vpp_max_mv, pulse_us; uint8_t max_pulses; } profile_t;',
        'static const profile_t profiles[PROFILE_COUNT] PROGMEM = {']
    for p in profiles:
        values=[p['size_bytes'],p['address_bits'],int(p['read_supported']),int(p['program_supported']),int(p['program_algorithm_verified']),4750,5250,
            int(p.get('program_vcc_min',0)*1000),int(p.get('program_vcc_max',0)*1000),int(p.get('program_vpp_min',0)*1000),
            int(p.get('program_vpp_max',0)*1000),p['program_pulse_us'] or 0,p['max_program_pulses'] or 0]
        header.append('  {"'+p['name']+'", '+', '.join(map(str,values))+'},')
    header+=['};','']
    (ROOT/'firmware'/'profiles.h').write_text('\n'.join(header),encoding='utf8')
    print('Profile hash:',digest,'profiles:',len(profiles))
if __name__=='__main__':generate()
